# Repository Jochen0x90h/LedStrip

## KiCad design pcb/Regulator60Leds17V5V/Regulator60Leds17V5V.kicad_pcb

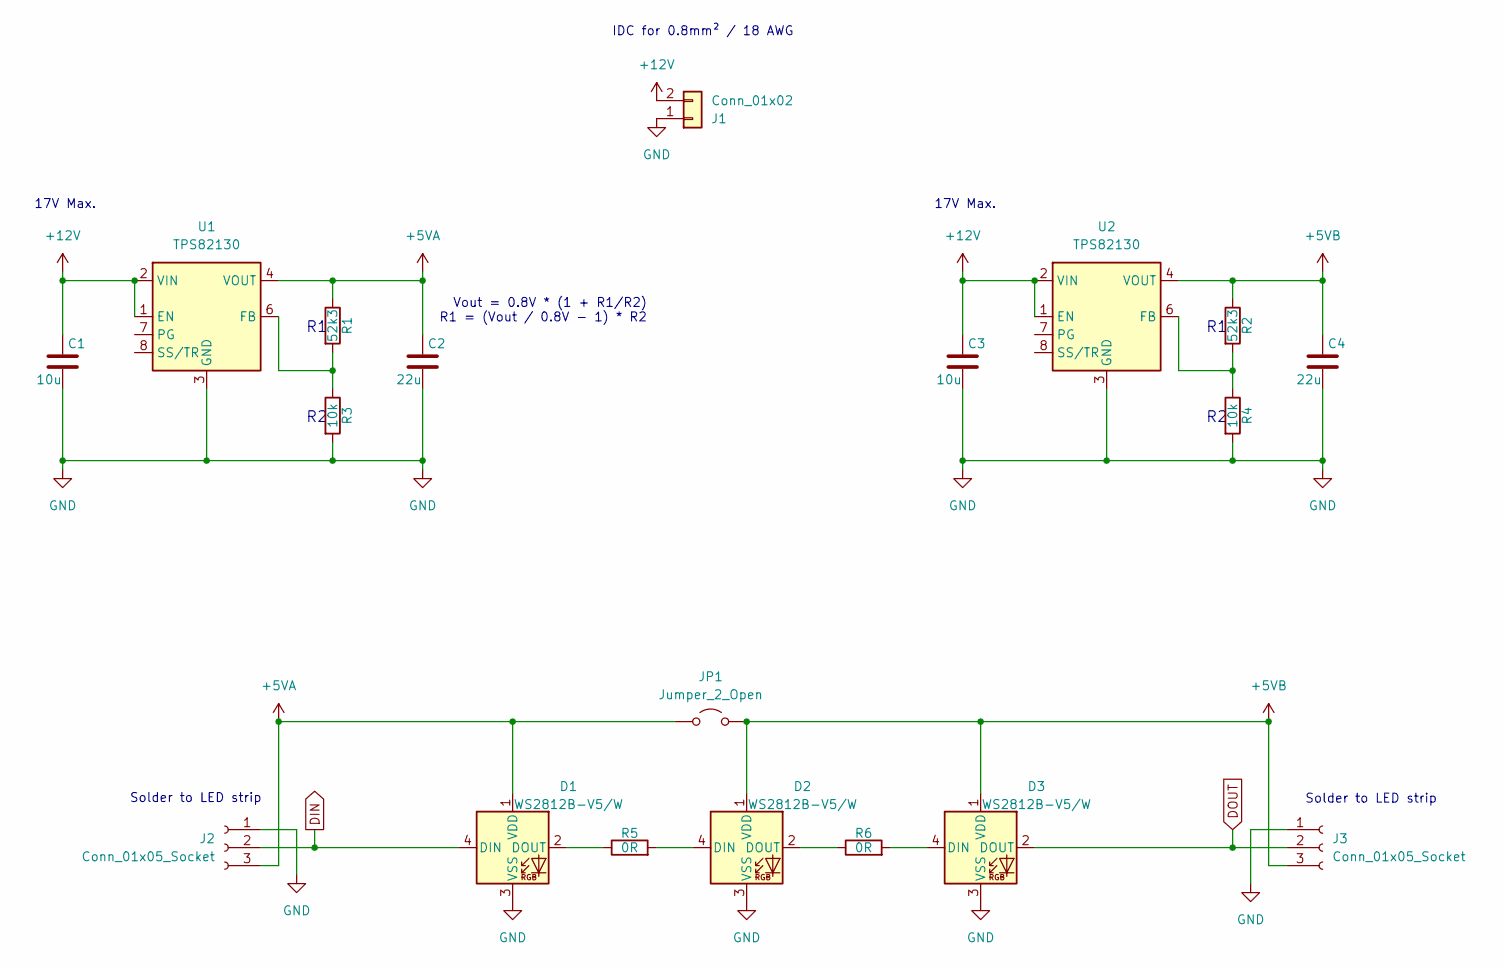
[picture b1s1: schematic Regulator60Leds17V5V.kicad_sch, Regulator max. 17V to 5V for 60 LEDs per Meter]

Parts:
C1, C3: 10u; 1206; MPN CL31A106KBHNNNE; LCSC PN C13585
C2, C4: 22u; 0805; MPN CL21A226MAQNNNE; LCSC PN C45783
D1, D2, D3: WS2812B-V5/W; WS2812B; MPN WS2812B-V5/W; LCSC PN C2874885
J1: Conn_01x02; Kyocera-009176002001906
J2, J3: Conn_01x05_Socket; SolderPads3pin3mm
JP1: Jumper_2_Open; Jumper
R1, R2: 52k3; 0603; MPN 0603WAF5232T5E; LCSC PN C23198
R3, R4: 10k; 0603; MPN 0603WAF1002T5E; LCSC PN C25804
R5, R6: 0R; 1206; MPN 1206W4F0000T5E; LCSC PN C17888
U1, U2: TPS82130; MPN TPS82130SILR; LCSC PN C473914

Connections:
+5VA: C2.1, D1.1 (VDD), J2.3, JP1.1 (A), R1.1, U1.4 (VOUT), U1.5 (VOUT)
+5VB: C4.1, D2.1 (VDD), D3.1 (VDD), J3.3, JP1.2 (B), R2.1, U2.4 (VOUT), U2.5 (VOUT)
+12V: C1.1, C3.1, J1.2, U1.1 (EN), U1.2 (VIN), U2.1 (EN), U2.2 (VIN)
DIN: D1.4 (DIN), J2.2
DOUT: D3.2 (DOUT), J3.2
GND: C1.2, C2.2, C3.2, C4.2, D1.3 (VSS), D2.3 (VSS), D3.3 (VSS), J1.1, J2.1, J3.1, R3.2, R4.2, U1.3 (GND), U1.9 (GND), U2.3 (GND), U2.9 (GND)
unnamed: D1.2 (DOUT), R5.1
unnamed: D2.4 (DIN), R5.2
unnamed: D2.2 (DOUT), R6.1
unnamed: D3.4 (DIN), R6.2
unnamed: R1.2, R3.1, U1.6 (FB)
unnamed: R2.2, R4.1, U2.6 (FB)

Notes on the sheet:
17V Max.
Vout = 0.8V * (1 + R1/R2) R1 = (Vout / 0.8V - 1) * R2
Solder to LED strip
IDC for 0.8mm² / 18 AWG

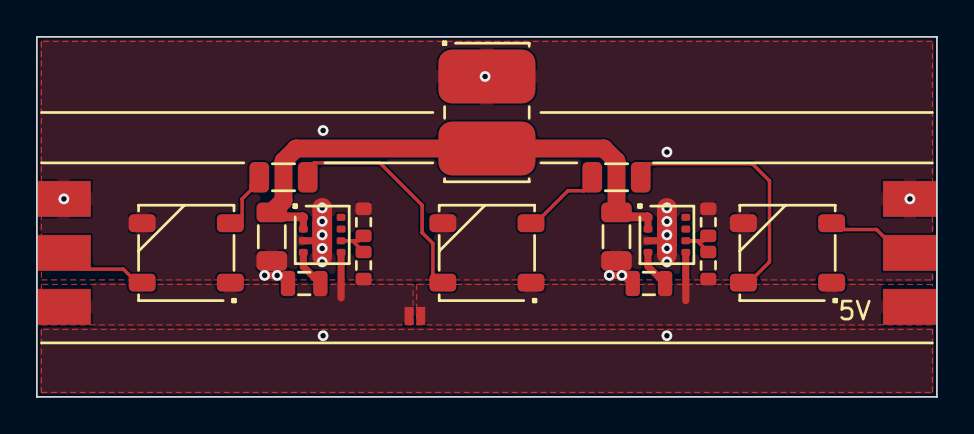
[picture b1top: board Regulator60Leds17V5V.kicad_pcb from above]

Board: 4 copper layers, 50.0 x 20.0 mm, 19 parts (0 on the bottom side), 12 nets.

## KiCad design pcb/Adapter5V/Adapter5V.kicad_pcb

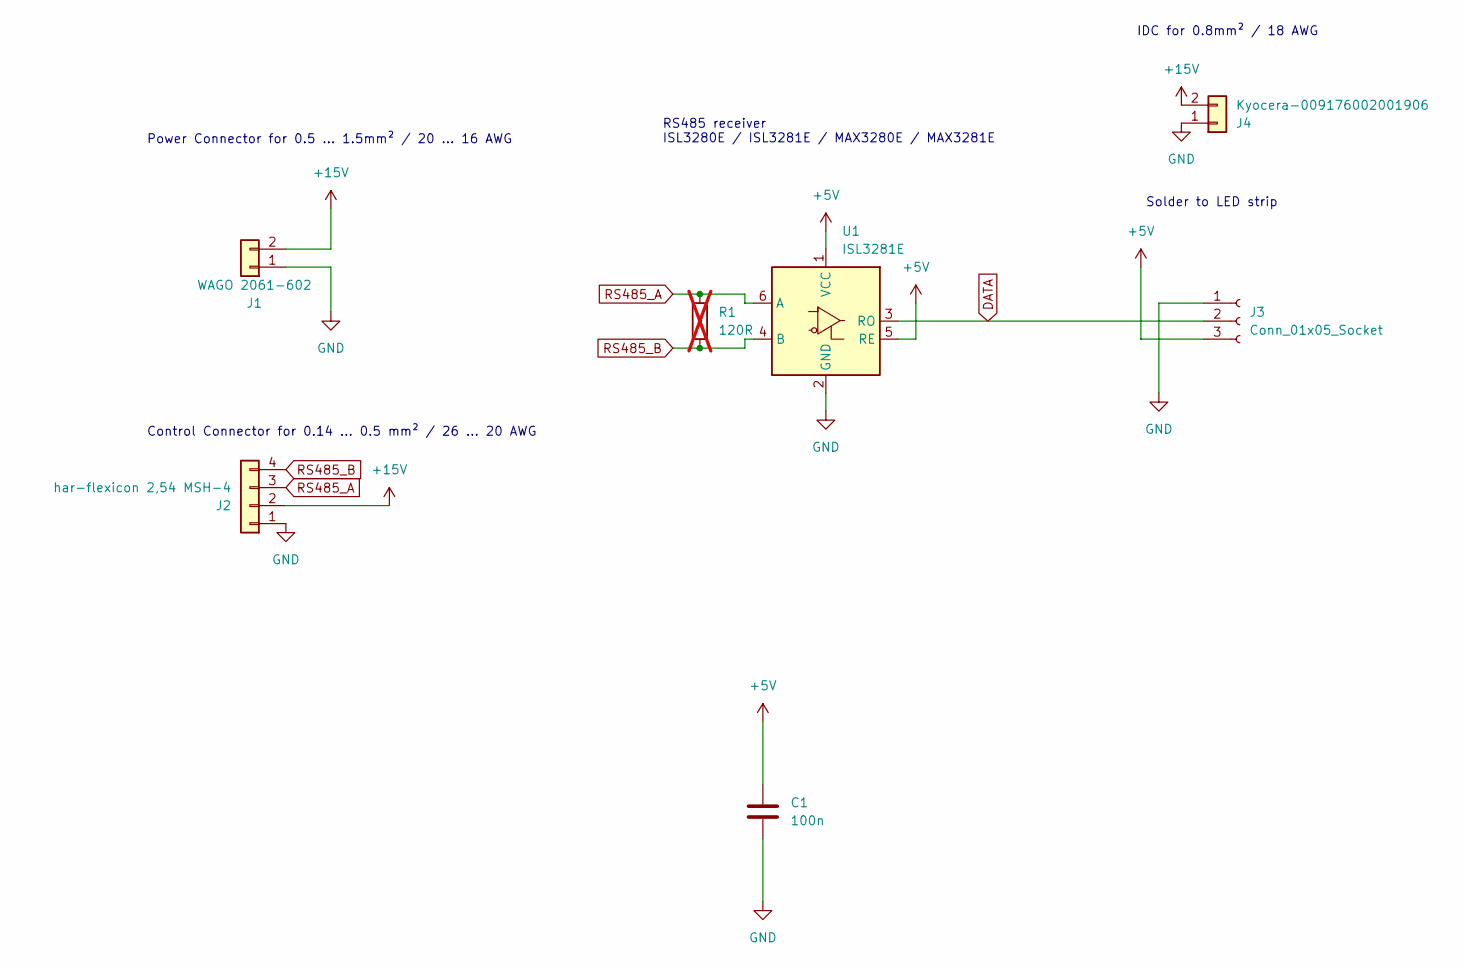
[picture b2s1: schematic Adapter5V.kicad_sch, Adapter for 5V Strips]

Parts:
C1: 100n; 0603
J1: WAGO 2061-602; WAGO2061-602
J2: har-flexicon 2,54 MSH-4; Harting14110413002000
J3: Conn_01x05_Socket; SolderHoles3pin3mm
J4: Kyocera-009176002001906
R1: 120R; 1206; not fitted
U1: ISL3281E

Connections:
+5V: C1.1, J3.3, U1.1 (VCC), U1.5 (RE)
+15V: J1.2, J2.2, J4.2
DATA: J3.2, U1.3 (RO)
GND: C1.2, J1.1, J2.1, J3.1, J4.1, U1.2 (GND)
RS485_A: J2.3, R1.1, U1.6 (A)
RS485_B: J2.4, R1.2, U1.4 (B)

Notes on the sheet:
IDC for 0.8mm² / 18 AWG
Control Connector for 0.14 … 0.5 mm² / 26 … 20 AWG
RS485 receiver ISL3280E / ISL3281E / MAX3280E / MAX3281E
Solder to LED strip
Power Connector for 0.5 … 1.5mm² / 20 … 16 AWG

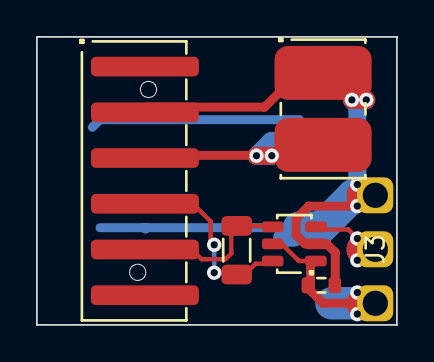
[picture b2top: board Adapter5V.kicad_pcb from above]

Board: 2 copper layers, 20.0 x 16.0 mm, 7 parts (1 on the bottom side), 6 nets.

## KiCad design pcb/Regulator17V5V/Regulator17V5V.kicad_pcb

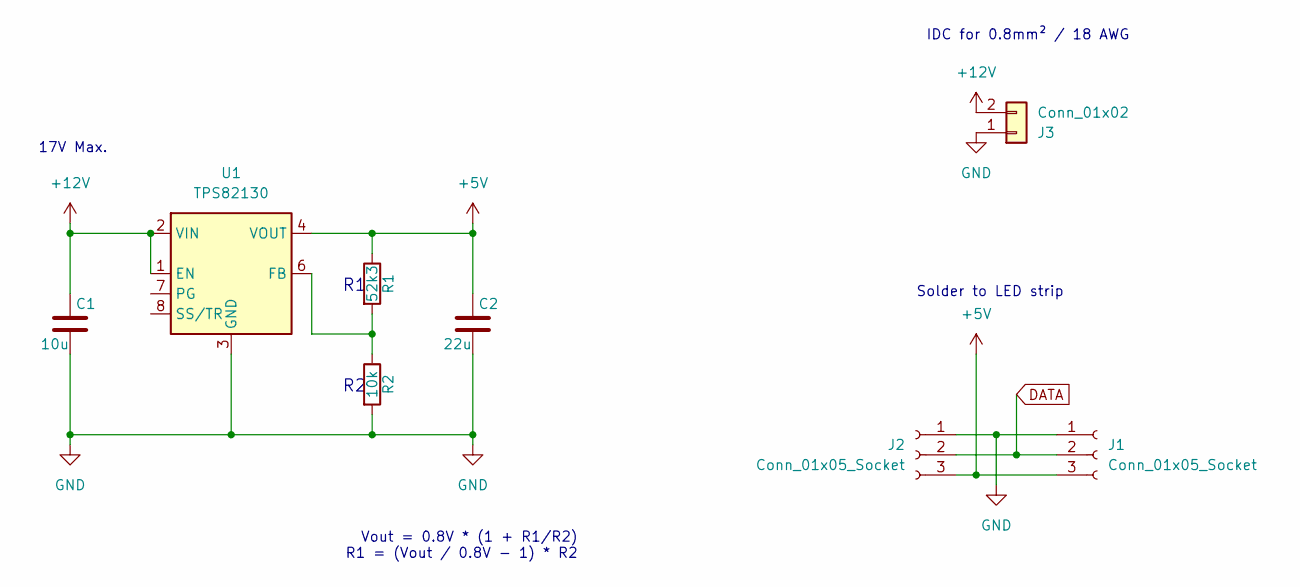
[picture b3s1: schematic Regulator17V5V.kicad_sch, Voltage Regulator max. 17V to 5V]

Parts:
C1: 10u; 1206
C2: 22u; 0805
J1, J2: Conn_01x05_Socket; SolderHoles3pin3mm
J3: Conn_01x02; Kyocera-009176002001906
R1: 52k3; 0603
R2: 10k; 0603
U1: TPS82130

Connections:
+5V: C2.1, J1.3, J2.3, R1.1, U1.4 (VOUT), U1.5 (VOUT)
+12V: C1.1, J3.2, U1.1 (EN), U1.2 (VIN)
DATA: J1.2, J2.2
GND: C1.2, C2.2, J1.1, J2.1, J3.1, R2.2, U1.3 (GND), U1.9 (GND)
unnamed: R1.2, R2.1, U1.6 (FB)

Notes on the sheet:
17V Max.
Vout = 0.8V * (1 + R1/R2) R1 = (Vout / 0.8V - 1) * R2
Solder to LED strip
IDC for 0.8mm² / 18 AWG

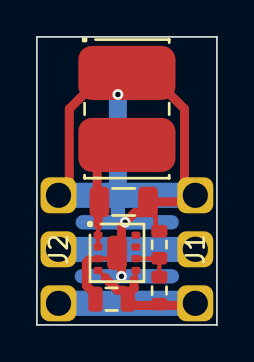
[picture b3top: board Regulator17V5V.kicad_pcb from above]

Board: 2 copper layers, 10.0 x 16.0 mm, 8 parts (0 on the bottom side), 5 nets.

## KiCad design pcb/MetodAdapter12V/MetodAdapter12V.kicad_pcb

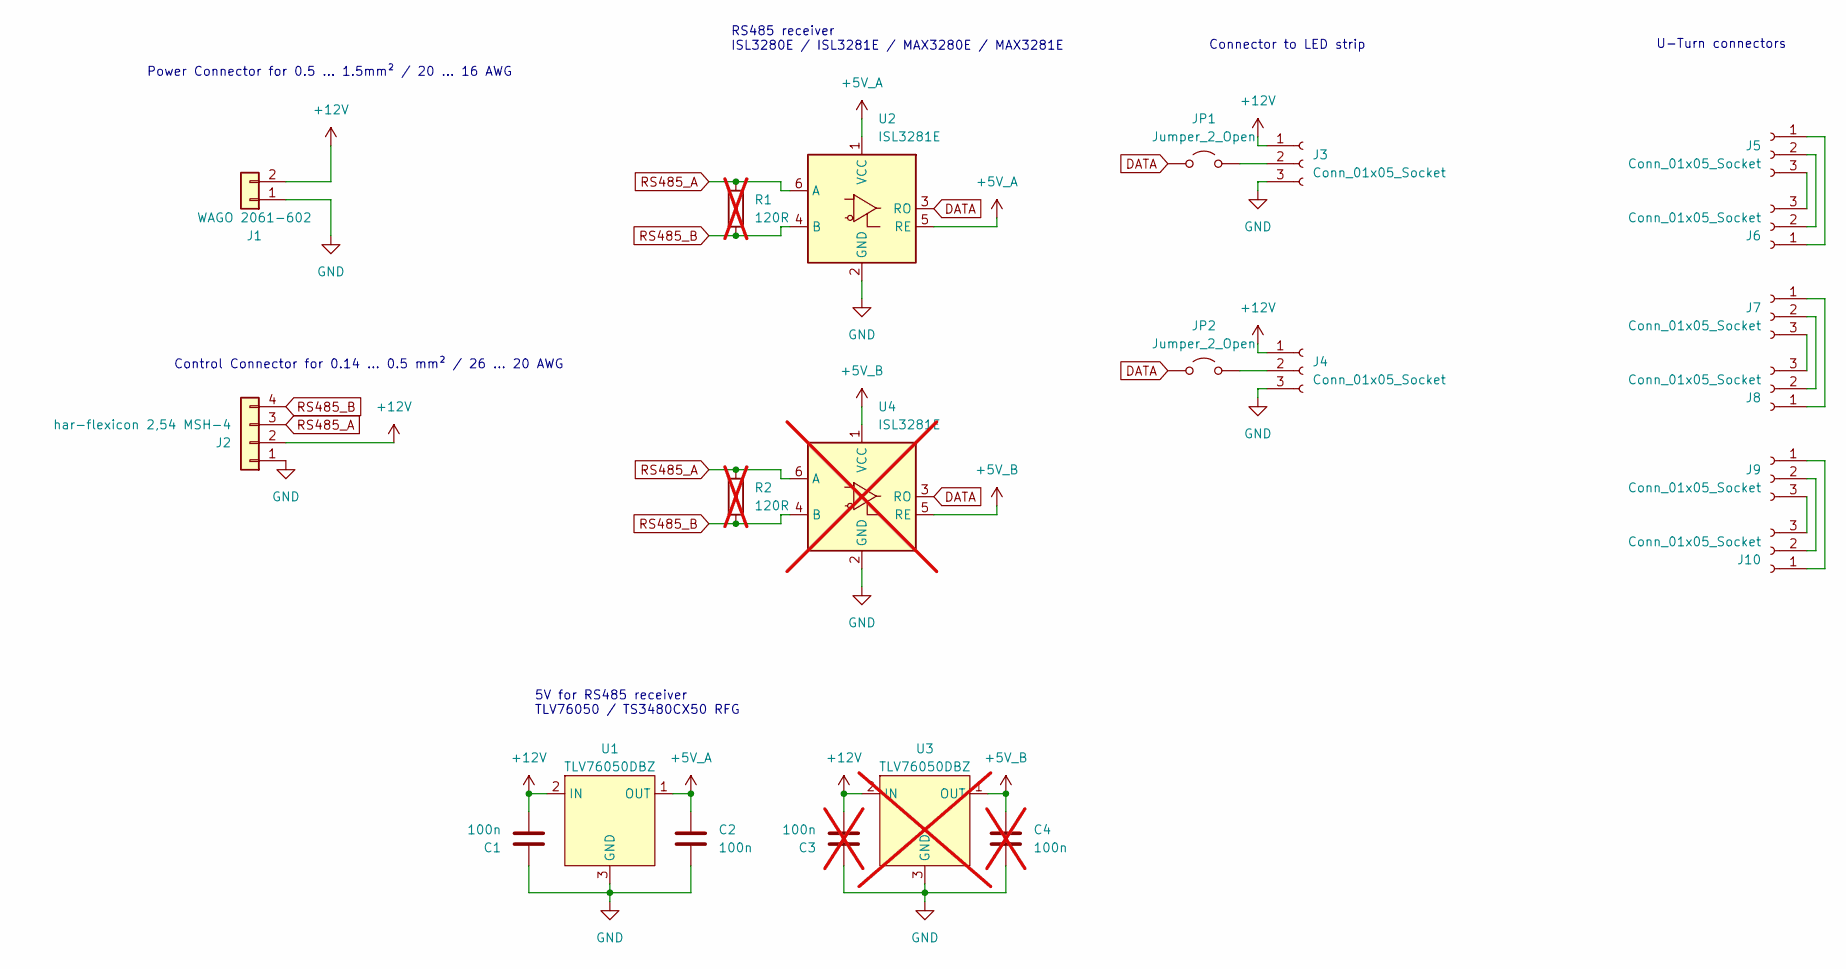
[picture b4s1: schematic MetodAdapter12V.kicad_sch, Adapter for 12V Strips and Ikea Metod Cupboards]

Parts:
C1, C2: 100n; 0603
C3, C4: 100n; 0603; not fitted
J1: WAGO 2061-602; WAGO2061-602
J2: har-flexicon 2,54 MSH-4; Harting14110413002000
J3, J4, J5, J6, J7, J8, J9, J10: Conn_01x05_Socket; LedConnector3pin3mm
JP1, JP2: Jumper_2_Open; Jumper
R1, R2: 120R; 1206; not fitted
U1: TLV76050DBZ; TI-DBZ
U2: ISL3281E
U3: TLV76050DBZ; TI-DBZ; not fitted
U4: ISL3281E; not fitted

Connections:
+5V_A: C2.1, U1.1 (OUT), U2.1 (VCC), U2.5 (RE)
+5V_B: C4.1, U3.1 (OUT), U4.1 (VCC), U4.5 (RE)
+12V: C1.2, C3.2, J1.2, J2.2, J3.1, J4.1, U1.2 (IN), U3.2 (IN)
DATA: JP1.1 (A), JP2.1 (A), U2.3 (RO), U4.3 (RO)
GND: C1.1, C2.2, C3.1, C4.2, J1.1, J2.1, J3.3, J4.3, U1.3 (GND), U2.2 (GND), U3.3 (GND), U4.2 (GND)
unnamed: J3.2, JP1.2 (B)
unnamed: J4.2, JP2.2 (B)
unnamed: J5.1, J6.1
unnamed: J5.2, J6.2
unnamed: J5.3, J6.3
unnamed: J7.1, J8.1
unnamed: J7.2, J8.2
unnamed: J7.3, J8.3
unnamed: J9.1, J10.1
unnamed: J9.2, J10.2
unnamed: J9.3, J10.3
RS485_A: J2.3, R1.1, R2.1, U2.6 (A), U4.6 (A)
RS485_B: J2.4, R1.2, R2.2, U2.4 (B), U4.4 (B)

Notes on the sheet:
5V for RS485 receiver TLV76050 / TS3480CX50 RFG
U-Turn connectors
RS485 receiver ISL3280E / ISL3281E / MAX3280E / MAX3281E
Control Connector for 0.14 … 0.5 mm² / 26 … 20 AWG
Connector to LED strip
Power Connector for 0.5 … 1.5mm² / 20 … 16 AWG

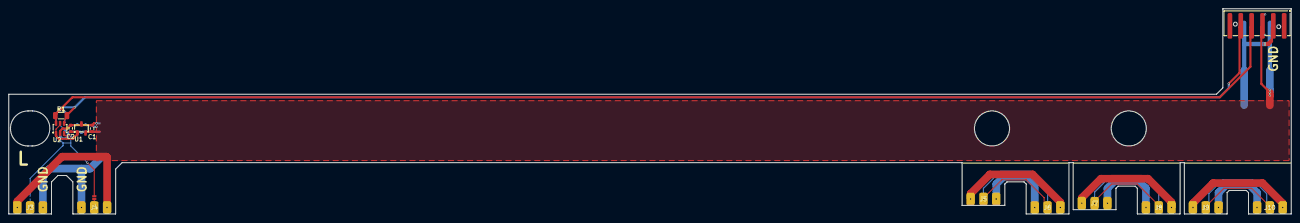
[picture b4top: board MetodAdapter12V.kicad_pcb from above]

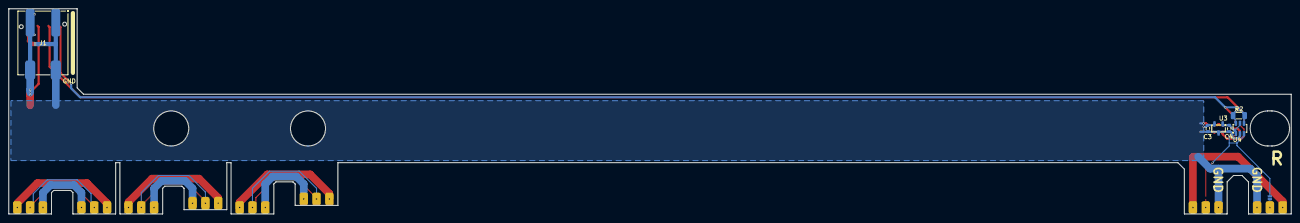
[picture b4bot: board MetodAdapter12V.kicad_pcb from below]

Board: 2 copper layers, 300.0 x 48.0 mm, 22 parts (7 on the bottom side), 18 nets.

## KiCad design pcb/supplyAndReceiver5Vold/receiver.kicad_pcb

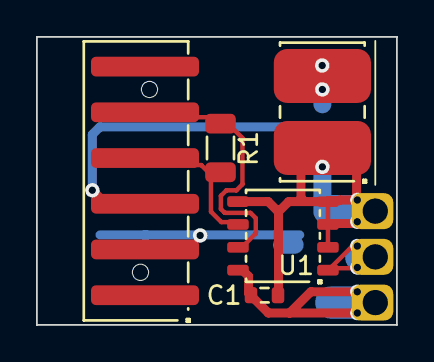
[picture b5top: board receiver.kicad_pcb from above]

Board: 2 copper layers, 20.0 x 16.0 mm, 7 parts (1 on the bottom side), 6 nets.

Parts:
C1: 100n; 0603
J1: WAGO 2061-602; WAGO2061-602
J2: har-flexicon 2,54 MSH-4; Harting14110413002000
J3: Conn_01x05_Socket; HolesL
J4: Kyocera-009176002001906
R1: 120R; 1206
U1: SP485CN; SO-8

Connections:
+5V: C1.1, J3.3, U1.8 (VCC)
+15V: J1.2, J2.2, J4.2
DATA: J3.2, U1.1 (RO)
GND: C1.2, J1.1, J2.1, J3.1, J4.1, U1.2 (~RE), U1.3 (DE), U1.4 (DI), U1.5 (GND)
RS485_A: J2.3, R1.1, U1.6 (A)
RS485_B: J2.4, R1.2, U1.7 (B)

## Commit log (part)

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2024-12-12 Use new FootprintTool
2024-12-12 Rename
2025-01-19 Add receiver for IKEA Metod cupboard
2025-04-14 Use ISL3280E
2025-05-01 New pin ordering for Harting connector
